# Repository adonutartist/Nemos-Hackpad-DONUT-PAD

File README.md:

<div align="center">

# Donut Pad :O

*A 12-key macropad with a rotary encoder and OLED display, built for Hack Club's Stardance YSWS.*

</div>

---

DEMO VIDEO: https://youtube.com/shorts/37Y9ueW4ZXs?feature=share

---

## About

Donut Pad is a 12 key macropad with a rotary encoder and an OLED display, built to function as a gamepad/game controller. It runs using a custom KiCad-designed PCB, and sits inside a integrated plate mounted case topped with a Kintsugi inspired plate with gold/silver cut accents.

## Features

- 12 Mechanical Keys:
  - 4 keys for D-Pad (Up, Down, Left, Right)
  - 4 keys for Action buttons (J, K, U, I)
  - Start and Esc buttons
  - Left and Right shoulder buttons
- EC11 Rotary Encoder for volume (rotation only press is not wired/functional)
- 128x32 OLED display (not functional)
- Seeed XIAO RP2040
- Clean custom PCB
- Sandwich mounting style case

---

## Exploded View

Everything fits together using 4 M3 screws and heatset inserts, integrated plate mount style, with 2 separate printed pieces:

- **Case Shell** where the PCB sits. Designed to be transparent so the PCB remains visible; clear resin printing (or transparent FDA) recommended for the best result. (I did it all black cuz resin is costly)
- **Case Top Plate** holds all keyholes, the OLED cutout, and the rotary encoder cutout. Features a black body with gold cut accents inspired by Kintsugi, the Japanese art of repairing broken pottery with gold.

Assembled view of Donut Pad:

Exploded view of Donut Pad:

Made in Fusion 360.

---

## BOM (Bill of Materials)

| Component | Qty | Purpose |
|-----------|-----|---------|
| Seeed XIAO RP2040 | 1 | Main controller |
| MX-Style switches | 12 | Key matrix |
| DSA keycaps | 12 | Keycaps |
| EC11 Rotary encoder | 1 | Scroll/volume input |
| 0.91" 128x32 OLED display | 1 | Status display |
| 1N4148 Diodes (THT) | 12 | Matrix ghosting protection |
| M3x16mm screws | 4 | Case assembly |
| M3x5x4mm heatset inserts | 4 | Case assembly |
| Custom PCB | 1 | — |
| 3D printed transparent case shell | 1 | Clear resin / transparent FDA |
| 3D printed Kintsugi-inspired case plate | 1 | Top plate with gold accents |

---

## Circuit Diagram

Designed in KiCad. The silkscreen art includes a custom dooOOnut mascot and the Hack Club logo.

PCB Schematic:

PCB Board:

---

## Known Issues

- **OLED display is not functional.** The PCB footprint was laid out assuming the module's pin header runs top-to-bottom (GND, 3V3, SCL, SDA), but the physical module's actual pin order runs bottom-to-top — so the connections ended up reversed on the board. Attempted a rework with a desoldering pump and solder wick to lift the header and rewire it with jumpers, but the pads wouldn't fully clear, so the fix was abandoned for now. Keys and the rotary encoder work fully; the OLED does not currently display anything.
- RGB underglow LEDs were dropped from the design due to DRC errors during PCB routing.

---

## Firmware

Built in the Arduino IDE using:

- Keyboard (built into the Raspberry Pi Pico/RP2040 board core)
- Adafruit GFX
- Adafruit SSD1306

Flash **`Macropad.ino`** to the board. The firmware:

- Scans the 4x3 matrix with debouncing and sends the mapped key on each press.
- Decodes the rotary encoder via interrupt-driven quadrature detection, sending Up/Down arrow keys.
- Drives the OLED status display — currently has no visible effect due to the wiring issue above, but the code is left in place for whenever the display gets rewired.

---

## OLED animation:

- Animated GIF on the OLED.

WIP preview of the OLED animation:

I might add more stuff in the future! That's it for now.

---

## Gallery

<table>
<tr>
<td width="50%">

</td>
<td width="50%">

</td>
</tr>

<tr>
<td width="50%">

</td>
<td width="50%">

</td>
</tr>

<tr>
<td width="50%">

</td>
<td width="50%">

</td>
</tr>
</table>

---

<div align="center">

</div>

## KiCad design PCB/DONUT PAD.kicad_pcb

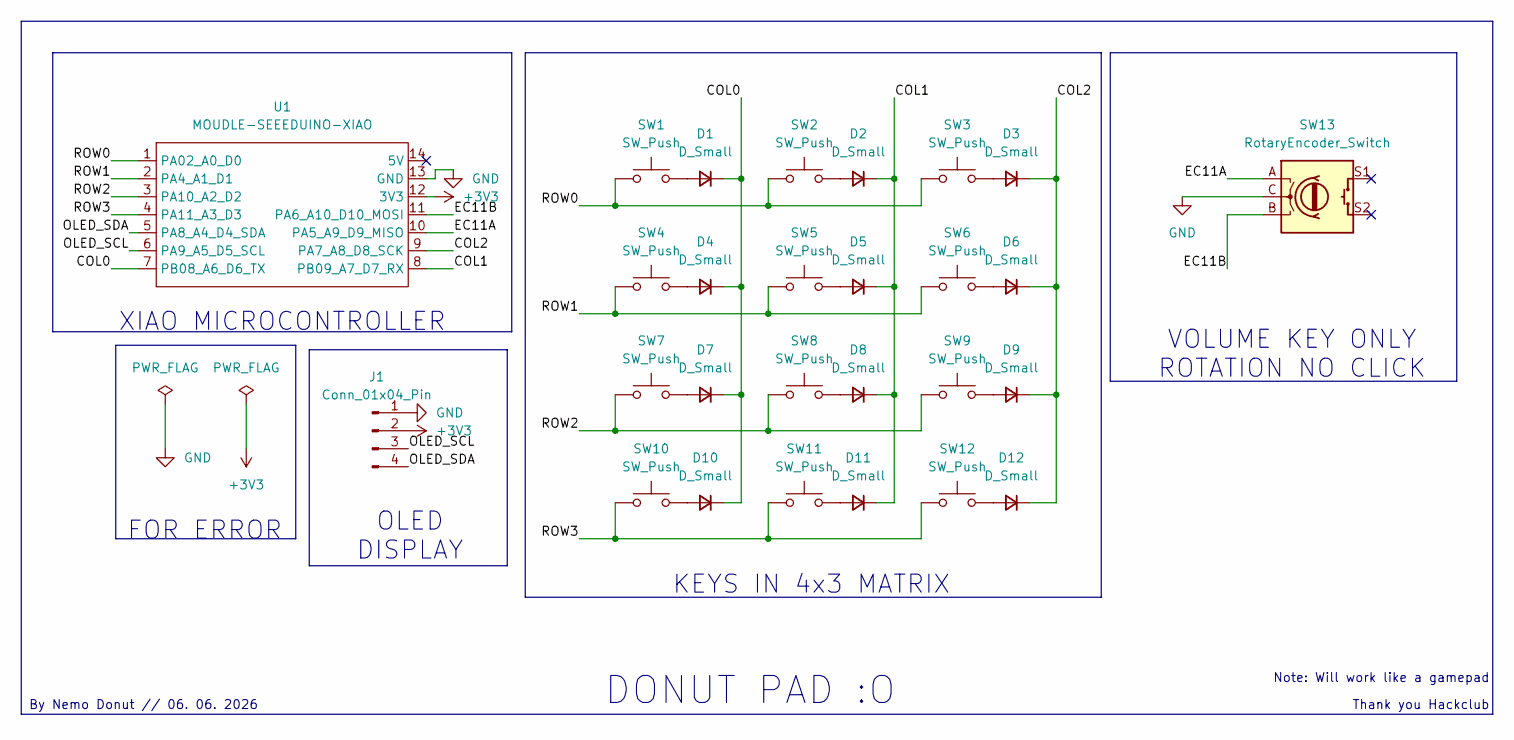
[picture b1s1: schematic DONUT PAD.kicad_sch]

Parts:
D1, D2, D3, D4, D5, D6, D7, D8, D9, D10, D11, D12: D_Small; D_DO-35_SOD27_P7.62mm_Horizontal
J1: Conn_01x04_Pin; PinHeader_1x04_P2.54mm_Vertical
SW1, SW2, SW3, SW4, SW5, SW6, SW7, SW8, SW9, SW10, SW11, SW12: SW_Push; SW_Cherry_MX_1.00u_PCB
SW13: RotaryEncoder_Switch; RotaryEncoder_Alps_EC11E-Switch_Vertical_H20mm
U1: MOUDLE-SEEEDUINO-XIAO; XIAO-Generic-Hybrid-14P-2.54-21X17.8MM

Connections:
+3V3: J1.2, U1.12 (3V3)
/COL0: D1.1 (K), D4.1 (K), D7.1 (K), D10.1 (K), U1.7 (PB08_A6_D6_TX)
/COL1: D2.1 (K), D5.1 (K), D8.1 (K), D11.1 (K), U1.8 (PB09_A7_D7_RX)
/COL2: D3.1 (K), D6.1 (K), D9.1 (K), D12.1 (K), U1.9 (PA7_A8_D8_SCK)
/EC11A: SW13.A, U1.10 (PA5_A9_D9_MISO)
/EC11B: SW13.B, U1.11 (PA6_A10_D10_MOSI)
/OLED_SCL: J1.3, U1.6 (PA9_A5_D5_SCL)
/OLED_SDA: J1.4, U1.5 (PA8_A4_D4_SDA)
/ROW0: SW1.1, SW2.1, SW3.1, U1.1 (PA02_A0_D0)
/ROW1: SW4.1, SW5.1, SW6.1, U1.2 (PA4_A1_D1)
/ROW2: SW7.1, SW8.1, SW9.1, U1.3 (PA10_A2_D2)
/ROW3: SW10.1, SW11.1, SW12.1, U1.4 (PA11_A3_D3)
GND: J1.1, SW13.C, U1.13 (GND)
unnamed: D1.2 (A), SW1.2
unnamed: D2.2 (A), SW2.2
unnamed: D3.2 (A), SW3.2
unnamed: D4.2 (A), SW4.2
unnamed: D5.2 (A), SW5.2
unnamed: D6.2 (A), SW6.2
unnamed: D7.2 (A), SW7.2
unnamed: D8.2 (A), SW8.2
unnamed: D9.2 (A), SW9.2
unnamed: D10.2 (A), SW10.2
unnamed: D11.2 (A), SW11.2
unnamed: D12.2 (A), SW12.2

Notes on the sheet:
Note: Will work like a gamepad
Thank you Hackclub
OLED DISPLAY
KEYS IN 4x3 MATRIX
VOLUME KEY ONLY ROTATION NO CLICK
DONUT PAD :O
By Nemo Donut // 06. 06. 2026
FOR ERROR
XIAO MICROCONTROLLER

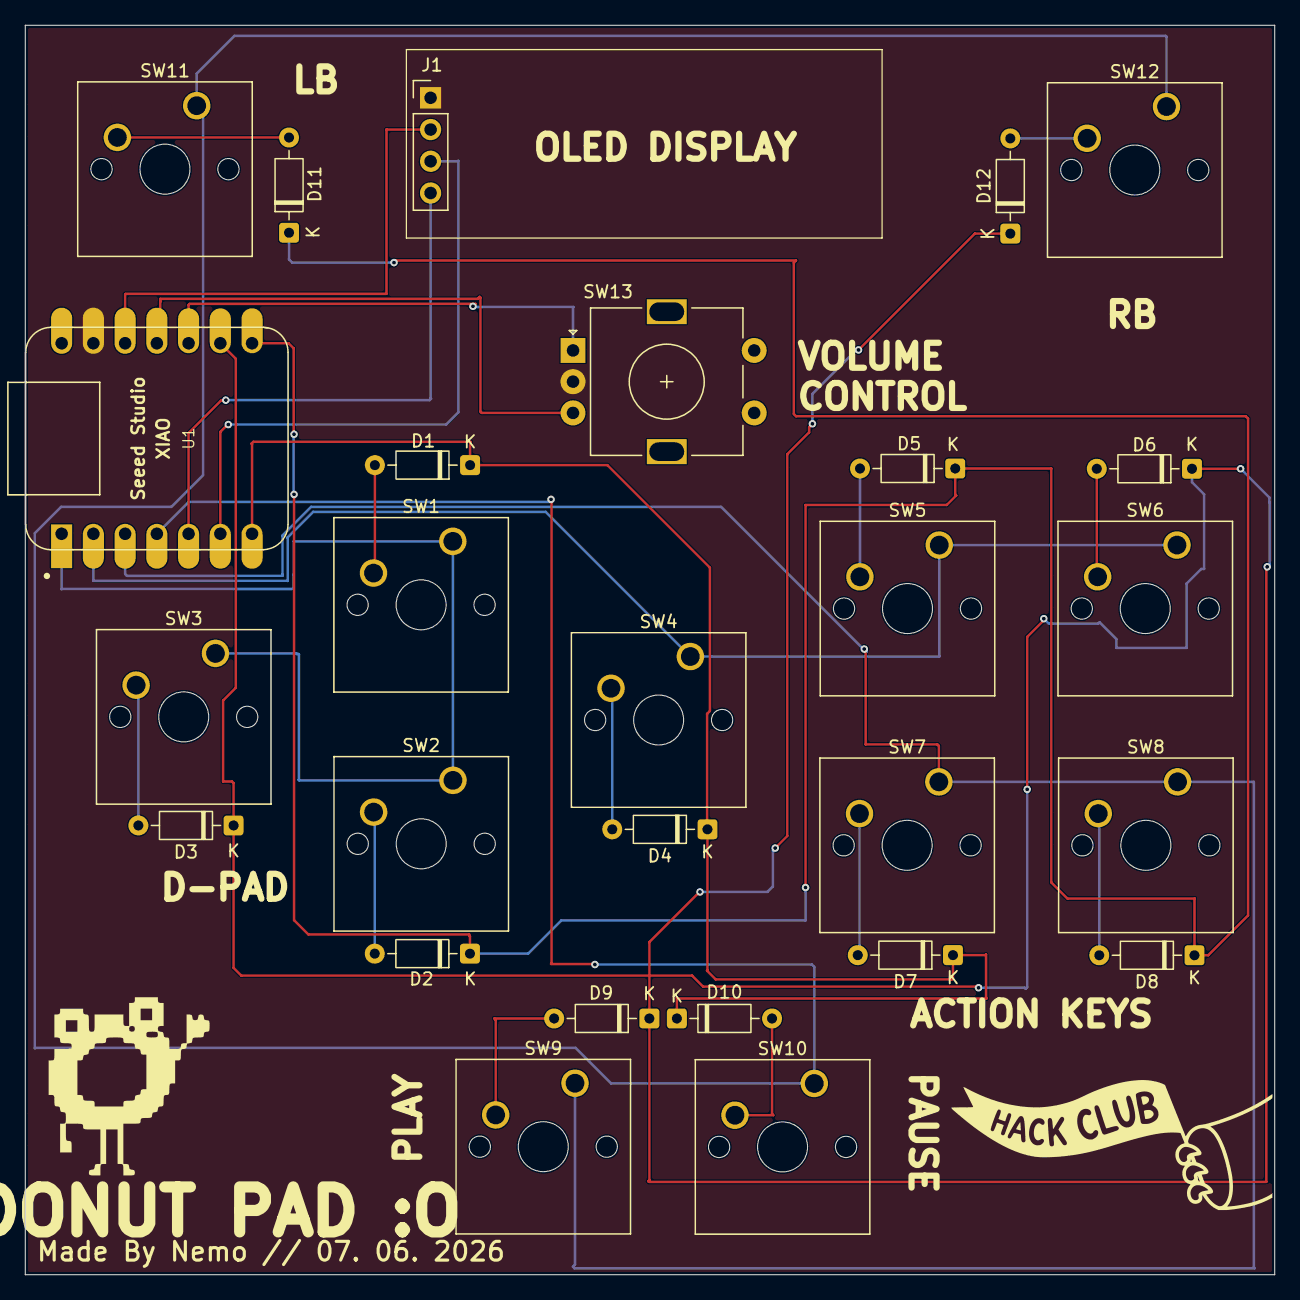
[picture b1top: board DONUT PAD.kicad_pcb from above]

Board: 2 copper layers, 100.0 x 100.0 mm, 27 parts (0 on the bottom side), 25 nets.

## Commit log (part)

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2026-06-13 test README.md
2026-06-14 firmware
2026-06-14 PCB uploaded
2026-06-14 production upload
2026-06-28 Add Bill of Materials for project components
